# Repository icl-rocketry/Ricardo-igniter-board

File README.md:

# Ricardo-igniter-board
Board that controls pyro channels and monitors pressure for engine igniter.

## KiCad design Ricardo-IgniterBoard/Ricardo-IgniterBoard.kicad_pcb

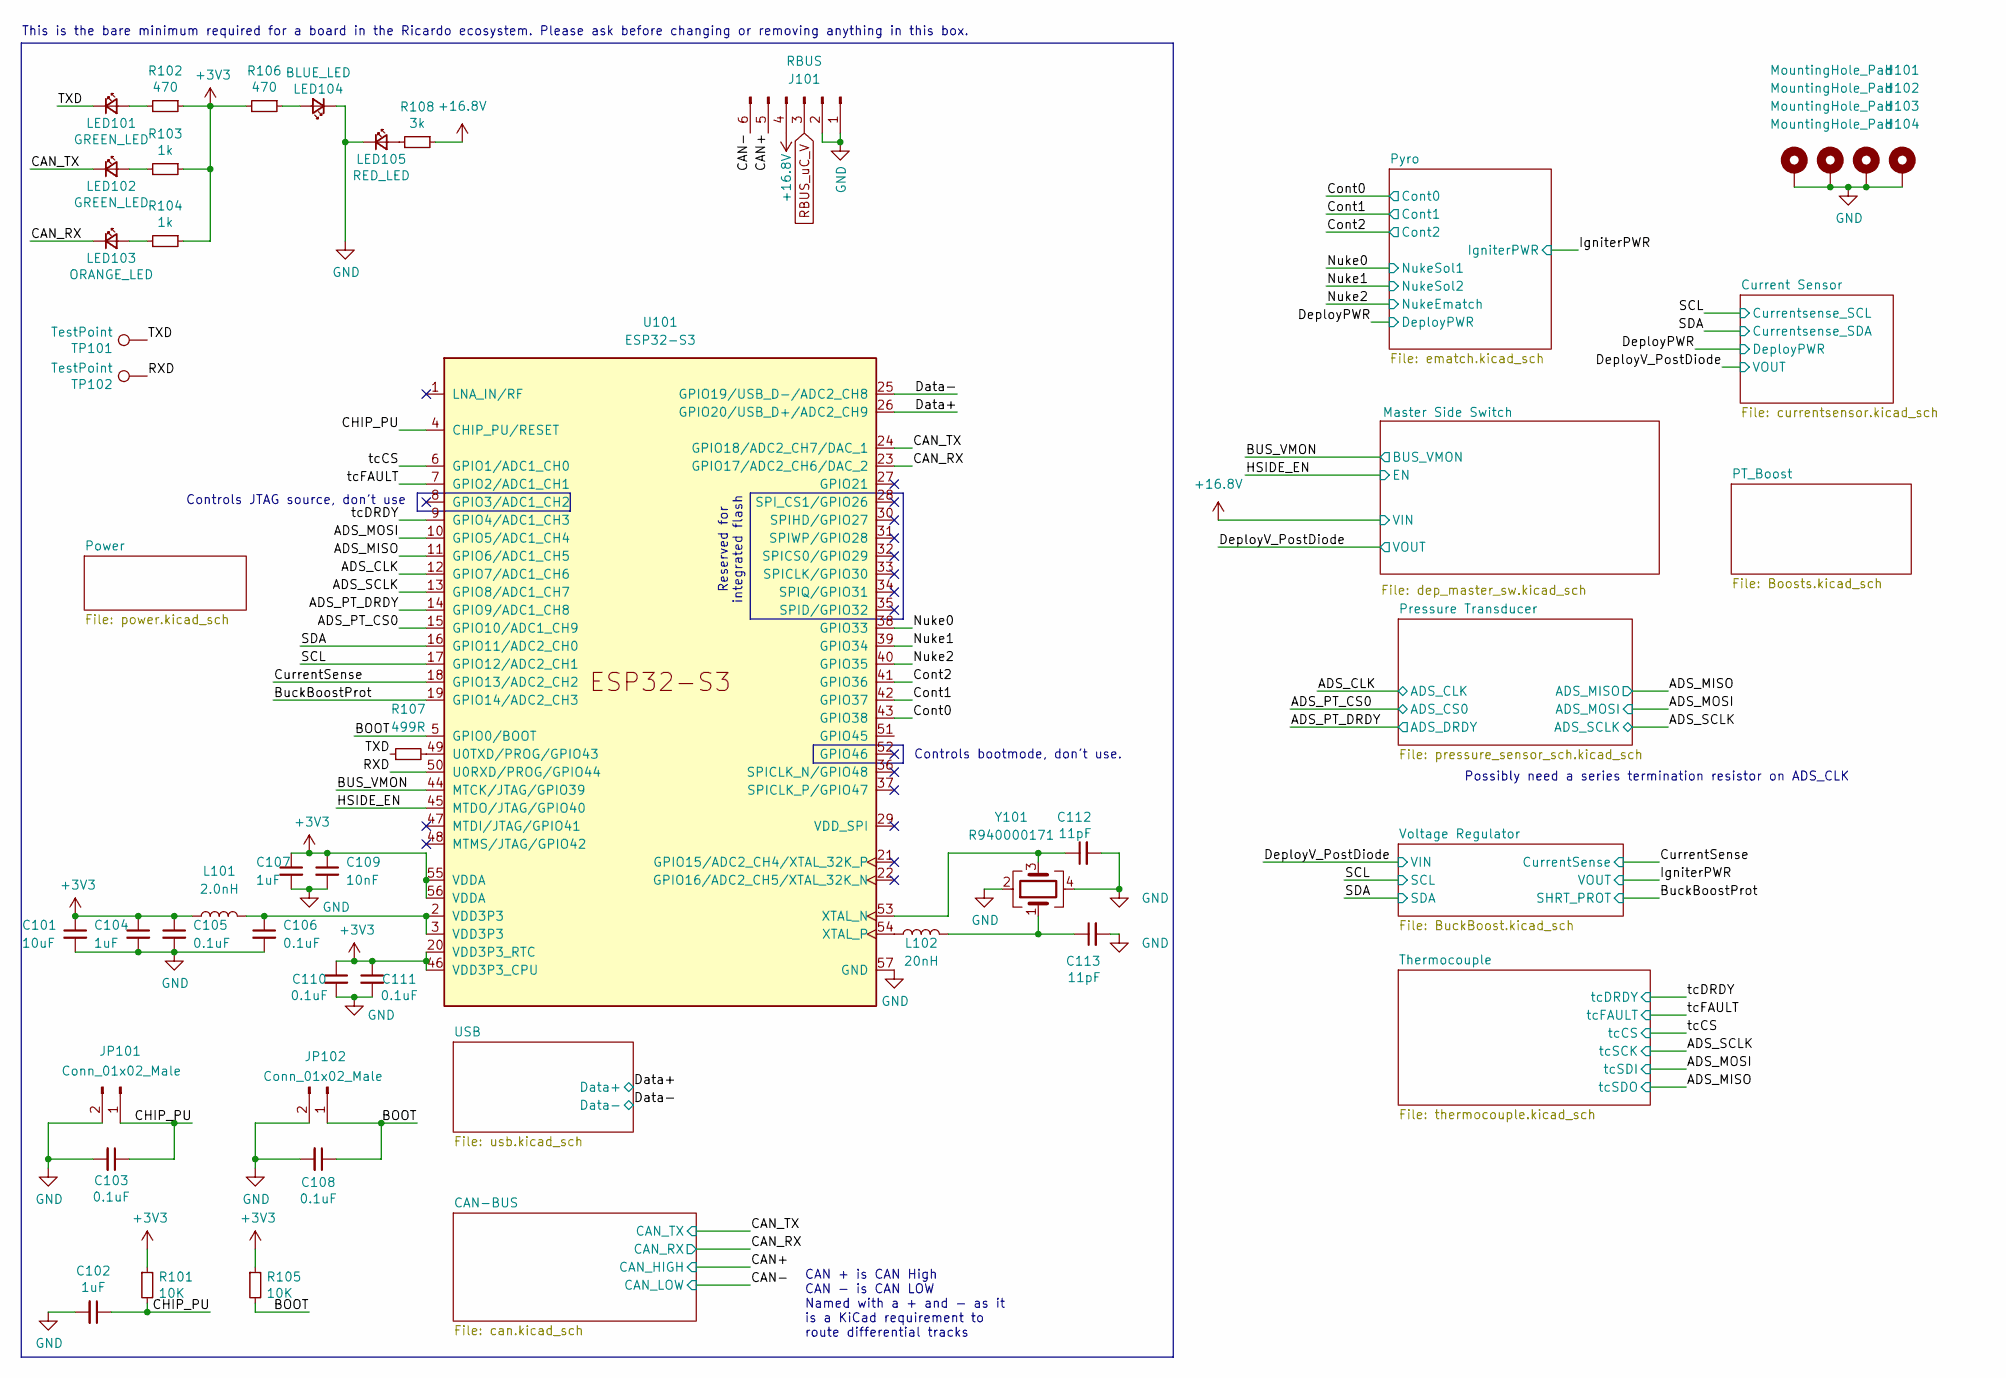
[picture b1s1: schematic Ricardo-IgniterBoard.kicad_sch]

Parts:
C101: 10uF; C_0402_1005Metric
C102, C104, C107: 1uF; C_0402_1005Metric
C103, C105, C106, C108, C110, C111: 0.1uF; C_0402_1005Metric
C109: 10nF; C_0402_1005Metric
C112, C113: 11pF; C_0402_1005Metric
H101, H102, H103, H104: MountingHole_Pad; MountingHole_3.2mm_M3_DIN965_Pad
J101: RBUS; Molex_Mini-Fit_Jr_5569-06A2_2x03_P4.20mm_Horizontal
JP101, JP102: Conn_01x02_Male; PinHeader_1x02_P2.54mm_Vertical
L101: 2.0nH; L_0402_1005Metric
L102: 20nH; L_0402_1005Metric
LED101, LED102: GREEN_LED; LED_0402_1005Metric
LED103: ORANGE_LED; LED_0402_1005Metric
LED104: BLUE_LED; LED_0402_1005Metric
LED105: RED_LED; LED_0402_1005Metric
R101, R105: 10K; R_0402_1005Metric
R102, R106: 470; R_0402_1005Metric
R103, R104: 1k; R_0402_1005Metric
R107: 499R; R_0402_1005Metric
R108: 3k; R_0402_1005Metric
TP101, TP102: TestPoint; TestPoint_Pad_D1.0mm
U101: ESP32-S3; QFN40P700X700X90-57N
Y101: R940000171; Crystal_SMD_2016-4Pin_2.0x1.6mm

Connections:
+3V3: C101.1, C104.1, C105.1, C107.1, C109.1, C110.1, C111.1, L101.1, R101.1, R102.1, R103.1, R104.1, R105.1, R106.2, U101.20 (VDD3P3_RTC), U101.46 (VDD3P3_CPU), U101.55 (VDDA), U101.56 (VDDA); also elsewhere on the board
+16.8V: J101.4, R108.1; also elsewhere on the board
/ADS_CLK: U101.12 (GPIO7/ADC1_CH6); also elsewhere on the board
/ADS_MISO: U101.11 (GPIO6/ADC1_CH5); also elsewhere on the board
/ADS_MOSI: U101.10 (GPIO5/ADC1_CH4); also elsewhere on the board
/ADS_PT_CS0: U101.15 (GPIO10/ADC1_CH9); also elsewhere on the board
/ADS_PT_DRDY: U101.14 (GPIO9/ADC1_CH8); also elsewhere on the board
/ADS_SCLK: U101.13 (GPIO8/ADC1_CH7); also elsewhere on the board
/BOOT: C108.1, JP102.1, R105.2, U101.5 (GPIO0/BOOT)
/BUS_VMON: U101.44 (MTCK/JTAG/GPIO39); also elsewhere on the board
/BuckBoostProt: U101.19 (GPIO14/ADC2_CH3); also elsewhere on the board
/CAN+: J101.5; also elsewhere on the board
/CAN-: J101.6; also elsewhere on the board
/CAN_RX: LED103.1 (K), U101.23 (GPIO17/ADC2_CH6/DAC_2); also elsewhere on the board
/CAN_TX: LED102.1 (K), U101.24 (GPIO18/ADC2_CH7/DAC_1); also elsewhere on the board
/CHIP_PU: C102.1, C103.1, JP101.1, R101.2, U101.4 (CHIP_PU/RESET)
/Cont0: U101.43 (GPIO38); also elsewhere on the board
/Cont1: U101.42 (GPIO37); also elsewhere on the board
/Cont2: U101.41 (GPIO36); also elsewhere on the board
/CurrentSense: U101.18 (GPIO13/ADC2_CH2); also elsewhere on the board
/Data+: U101.26 (GPIO20/USB_D+/ADC2_CH9); also elsewhere on the board
/Data-: U101.25 (GPIO19/USB_D-/ADC2_CH8); also elsewhere on the board
/HSIDE_EN: U101.45 (MTDO/JTAG/GPIO40); also elsewhere on the board
/Nuke0: U101.38 (GPIO33); also elsewhere on the board
/Nuke1: U101.39 (GPIO34); also elsewhere on the board
/Nuke2: U101.40 (GPIO35); also elsewhere on the board
/RXD: TP102.1, U101.50 (U0RXD/PROG/GPIO44)
/SCL: U101.17 (GPIO12/ADC2_CH1); also elsewhere on the board
/SDA: U101.16 (GPIO11/ADC2_CH0); also elsewhere on the board
/TXD: LED101.1 (K), R107.1, TP101.1
/tcCS: U101.6 (GPIO1/ADC1_CH0); also elsewhere on the board
/tcDRDY: U101.9 (GPIO4/ADC1_CH3); also elsewhere on the board
/tcFAULT: U101.7 (GPIO2/ADC1_CH1); also elsewhere on the board
GND: C101.2, C102.2, C103.2, C104.2, C105.2, C106.2, C107.2, C108.2, C109.2, C110.2, C111.2, C112.2, C113.2, H101.1, H102.1, H103.1, H104.1, J101.1, J101.2, JP101.2, JP102.2, LED104.1 (K), LED105.1 (K), U101.57 (GND), Y101.2, Y101.4; also elsewhere on the board
unnamed: C106.1, L101.2, U101.2 (VDD3P3), U101.3 (VDD3P3)
unnamed: C113.1, L102.2, Y101.1
unnamed: LED101.2 (A), R102.2
unnamed: LED102.2 (A), R103.2
unnamed: LED103.2 (A), R104.2
unnamed: LED104.2 (A), R106.1
unnamed: LED105.2 (A), R108.2
unnamed: R107.2, U101.49 (U0TXD/PROG/GPIO43)
unnamed: C112.1, U101.53 (XTAL_N), Y101.3
unnamed: L102.1, U101.54 (XTAL_P)
RBUS_uC_V: J101.3; also elsewhere on the board

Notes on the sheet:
Controls bootmode, don't use.
This is the bare minimum required for a board in the Ricardo ecosystem. Please ask before changing or removing anything in this box.
Possibly need a series termination resistor on ADS_CLK
CAN + is CAN High CAN - is CAN LOW Named with a + and - as it is a KiCad requirement to route differential tracks
Controls JTAG source, don't use
Reserved for integrated flash

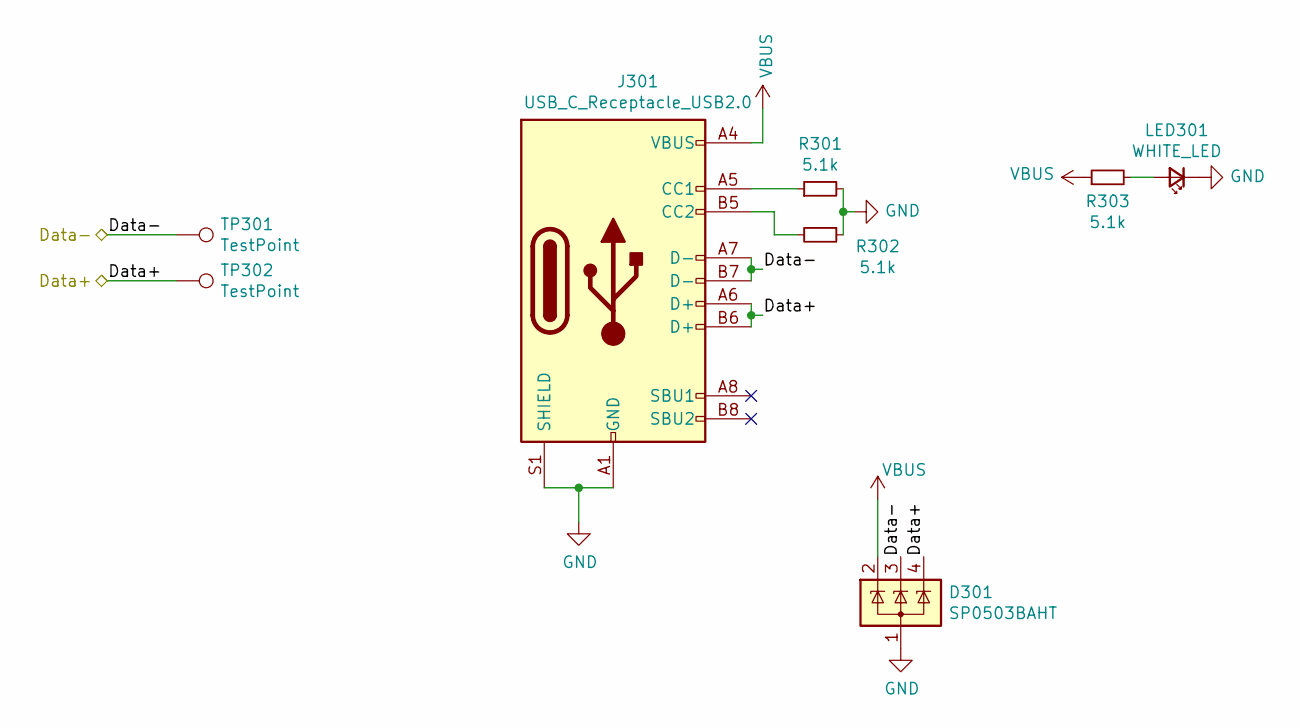
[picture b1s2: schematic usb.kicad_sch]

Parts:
D301: SP0503BAHT; SOT-143
J301: USB_C_Receptacle_USB2.0; USB_C_Receptacle_Palconn_UTC16-G
LED301: WHITE_LED; LED_0402_1005Metric
R301, R302, R303: 5.1k; R_0402_1005Metric
TP301, TP302: TestPoint; TestPoint_Pad_D1.0mm

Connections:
/Data+: D301.4 (K), J301.A6 (D+), J301.B6 (D+), TP302.1; also elsewhere on the board
/Data-: D301.3 (K), J301.A7 (D-), J301.B7 (D-), TP301.1; also elsewhere on the board
GND: D301.1 (A), J301.A1 (GND), J301.A12 (GND), J301.B1 (GND), J301.B12 (GND), J301.S1 (SHIELD), LED301.1 (K), R301.2, R302.1; also elsewhere on the board
unnamed: J301.A5 (CC1), R301.1
unnamed: J301.B5 (CC2), R302.2
unnamed: LED301.2 (A), R303.2
VBUS: D301.2 (K), J301.A4 (VBUS), J301.A9 (VBUS), J301.B4 (VBUS), J301.B9 (VBUS), R303.1; also elsewhere on the board

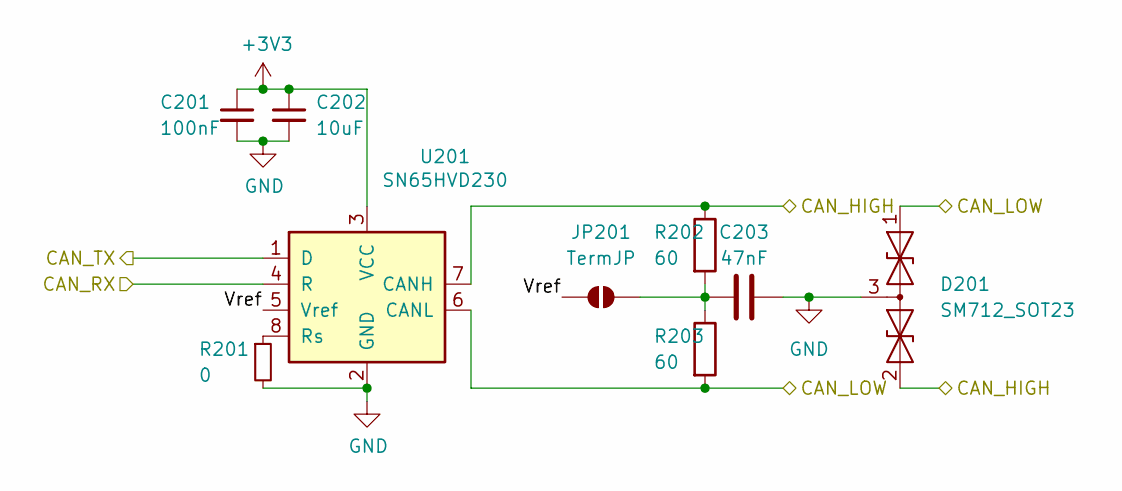
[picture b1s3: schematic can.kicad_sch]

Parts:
C201: 100nF; C_0402_1005Metric
C202: 10uF; C_0402_1005Metric
C203: 47nF; C_0402_1005Metric
D201: SM712_SOT23; SOT-23
JP201: TermJP; SmallerSolderJP
R201: 0; R_0603_1608Metric
R202, R203: 60; R_0603_1608Metric
U201: SN65HVD230; SOIC-8_3.9x4.9mm_P1.27mm

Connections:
+3V3: C201.1, C202.1, U201.3 (VCC); also elsewhere on the board
/CAN+: D201.2 (A2), R202.1, U201.7 (CANH); also elsewhere on the board
/CAN-: D201.1 (A1), R203.2, U201.6 (CANL); also elsewhere on the board
/CAN-BUS/Vref: JP201.1 (A), U201.5 (Vref)
/CAN_RX: U201.4 (R); also elsewhere on the board
/CAN_TX: U201.1 (D); also elsewhere on the board
GND: C201.2, C202.2, C203.2, D201.3 (common), R201.2, U201.2 (GND); also elsewhere on the board
unnamed: C203.1, JP201.2 (B), R202.2, R203.1
unnamed: R201.1, U201.8 (Rs)

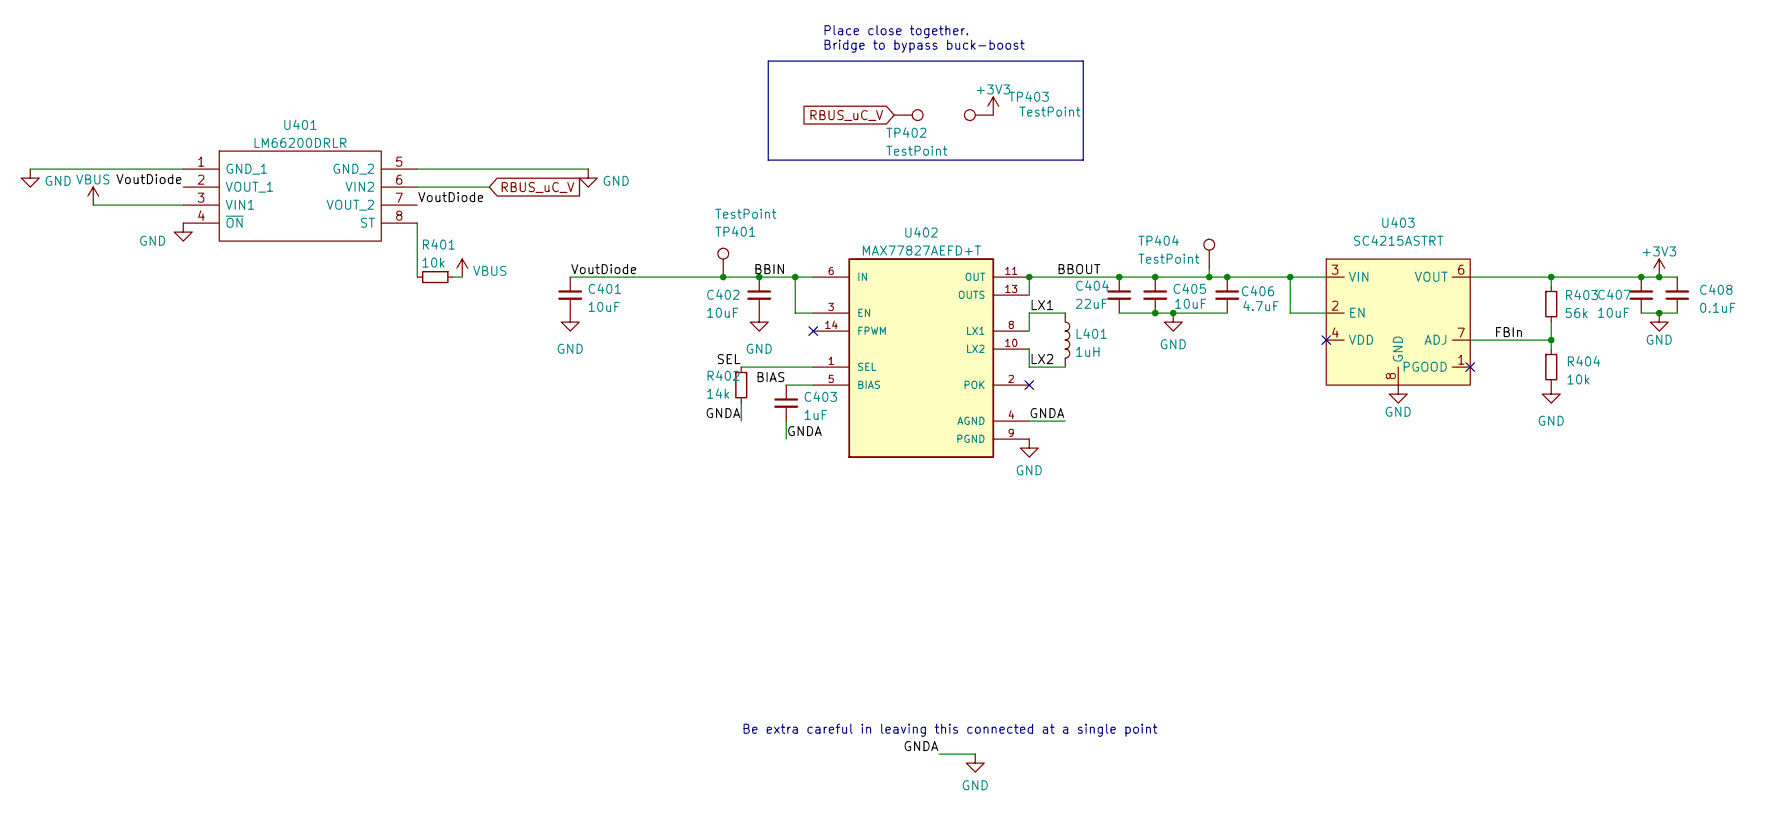
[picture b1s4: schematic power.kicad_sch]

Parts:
C401, C405, C407: 10uF; C_0402_1005Metric
C402: 10uF; C_0603_1608Metric
C403: 1uF; C_0402_1005Metric
C404: 22uF; C_0603_1608Metric
C406: 4.7uF; C_0402_1005Metric
C408: 0.1uF; C_0402_1005Metric
L401: 1uH; L_0805_2012Metric
R401, R404: 10k; R_0402_1005Metric
R402: 14k; R_0402_1005Metric
R403: 56k; R_0402_1005Metric
TP401, TP402, TP403, TP404: TestPoint; TestPoint_Pad_D1.5mm
U401: LM66200DRLR; SOTFL50P160X60-8N; Manufacturer_Part_Number LM66200DRLR; Mouser Part Number 595-LM66200DRLR
U402: MAX77827AEFD+T; CONV_MAX77827AEFD+T; PARTREV B
U403: SC4215ASTRT; SOIC127P599X175-9N

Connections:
+3V3: C407.2, C408.2, R403.1, TP403.1, U403.6 (VOUT); also elsewhere on the board
/Power/BBIN: C401.1, C402.1, TP401.1, U401.2 (VOUT_1), U401.7 (VOUT_2), U402.3 (EN), U402.6 (IN)
/Power/BBOUT: C404.1, C405.1, C406.1, TP404.1, U402.11 (OUT), U402.13 (OUTS), U403.2 (EN), U403.3 (VIN)
/Power/BIAS: C403.1, U402.5 (BIAS)
/Power/FBIn: R403.2, R404.1, U403.7 (ADJ)
/Power/LX1: L401.1, U402.8 (LX1)
/Power/LX2: L401.2, U402.10 (LX2)
/Power/SEL: R402.1, U402.1 (SEL)
GND: C401.2, C402.2, C403.2, C404.2, C405.2, C406.2, C407.1, C408.1, R402.2, R404.2, U401.1 (GND_1), U401.4 (~ON), U401.5 (GND_2), U402.4 (AGND), U402.9 (PGND), U403.8 (GND), U403.9 (GND); also elsewhere on the board
unnamed: R401.2, U401.8 (ST)
RBUS_uC_V: TP402.1, U401.6 (VIN2); also elsewhere on the board
VBUS: R401.1, U401.3 (VIN1); also elsewhere on the board

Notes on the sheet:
Place close together. Bridge to bypass buck-boost
Be extra careful in leaving this connected at a single point

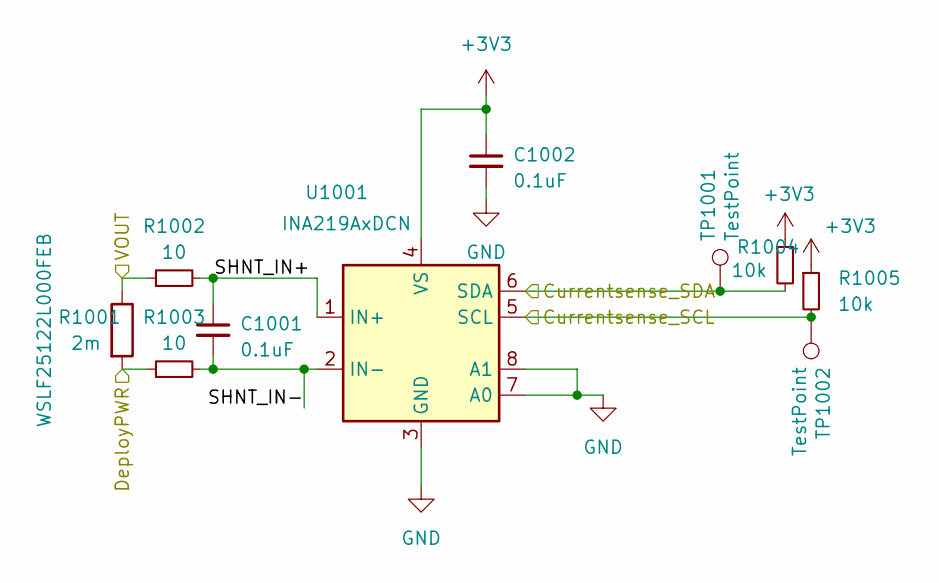
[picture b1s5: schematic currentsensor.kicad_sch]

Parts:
C1001, C1002: 0.1uF; C_0402_1005Metric
R1001: 2m; R_2512_6332Metric_Pad1.40x3.35mm_HandSolder; MPN WSLF25122L000FEB
R1002, R1003: 10; R_0402_1005Metric
R1004, R1005: 10k; R_0402_1005Metric
TP1001, TP1002: TestPoint; TestPoint_Pad_D1.0mm
U1001: INA219AxDCN; SOT-23-8

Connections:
+3V3: C1002.1, R1004.1, R1005.1, U1001.4 (VS); also elsewhere on the board
/Current Sensor/SHNT_IN+: C1001.1, R1002.2, U1001.1 (IN+)
/Current Sensor/SHNT_IN-: C1001.2, R1003.2, U1001.2 (IN-)
/DeployPWR: R1001.2, R1003.1; also elsewhere on the board
/DeployV_PostDiode: R1001.1, R1002.1; also elsewhere on the board
/SCL: R1005.2, TP1002.1, U1001.5 (SCL); also elsewhere on the board
/SDA: R1004.2, TP1001.1, U1001.6 (SDA); also elsewhere on the board
GND: C1002.2, U1001.3 (GND), U1001.7 (A0), U1001.8 (A1); also elsewhere on the board

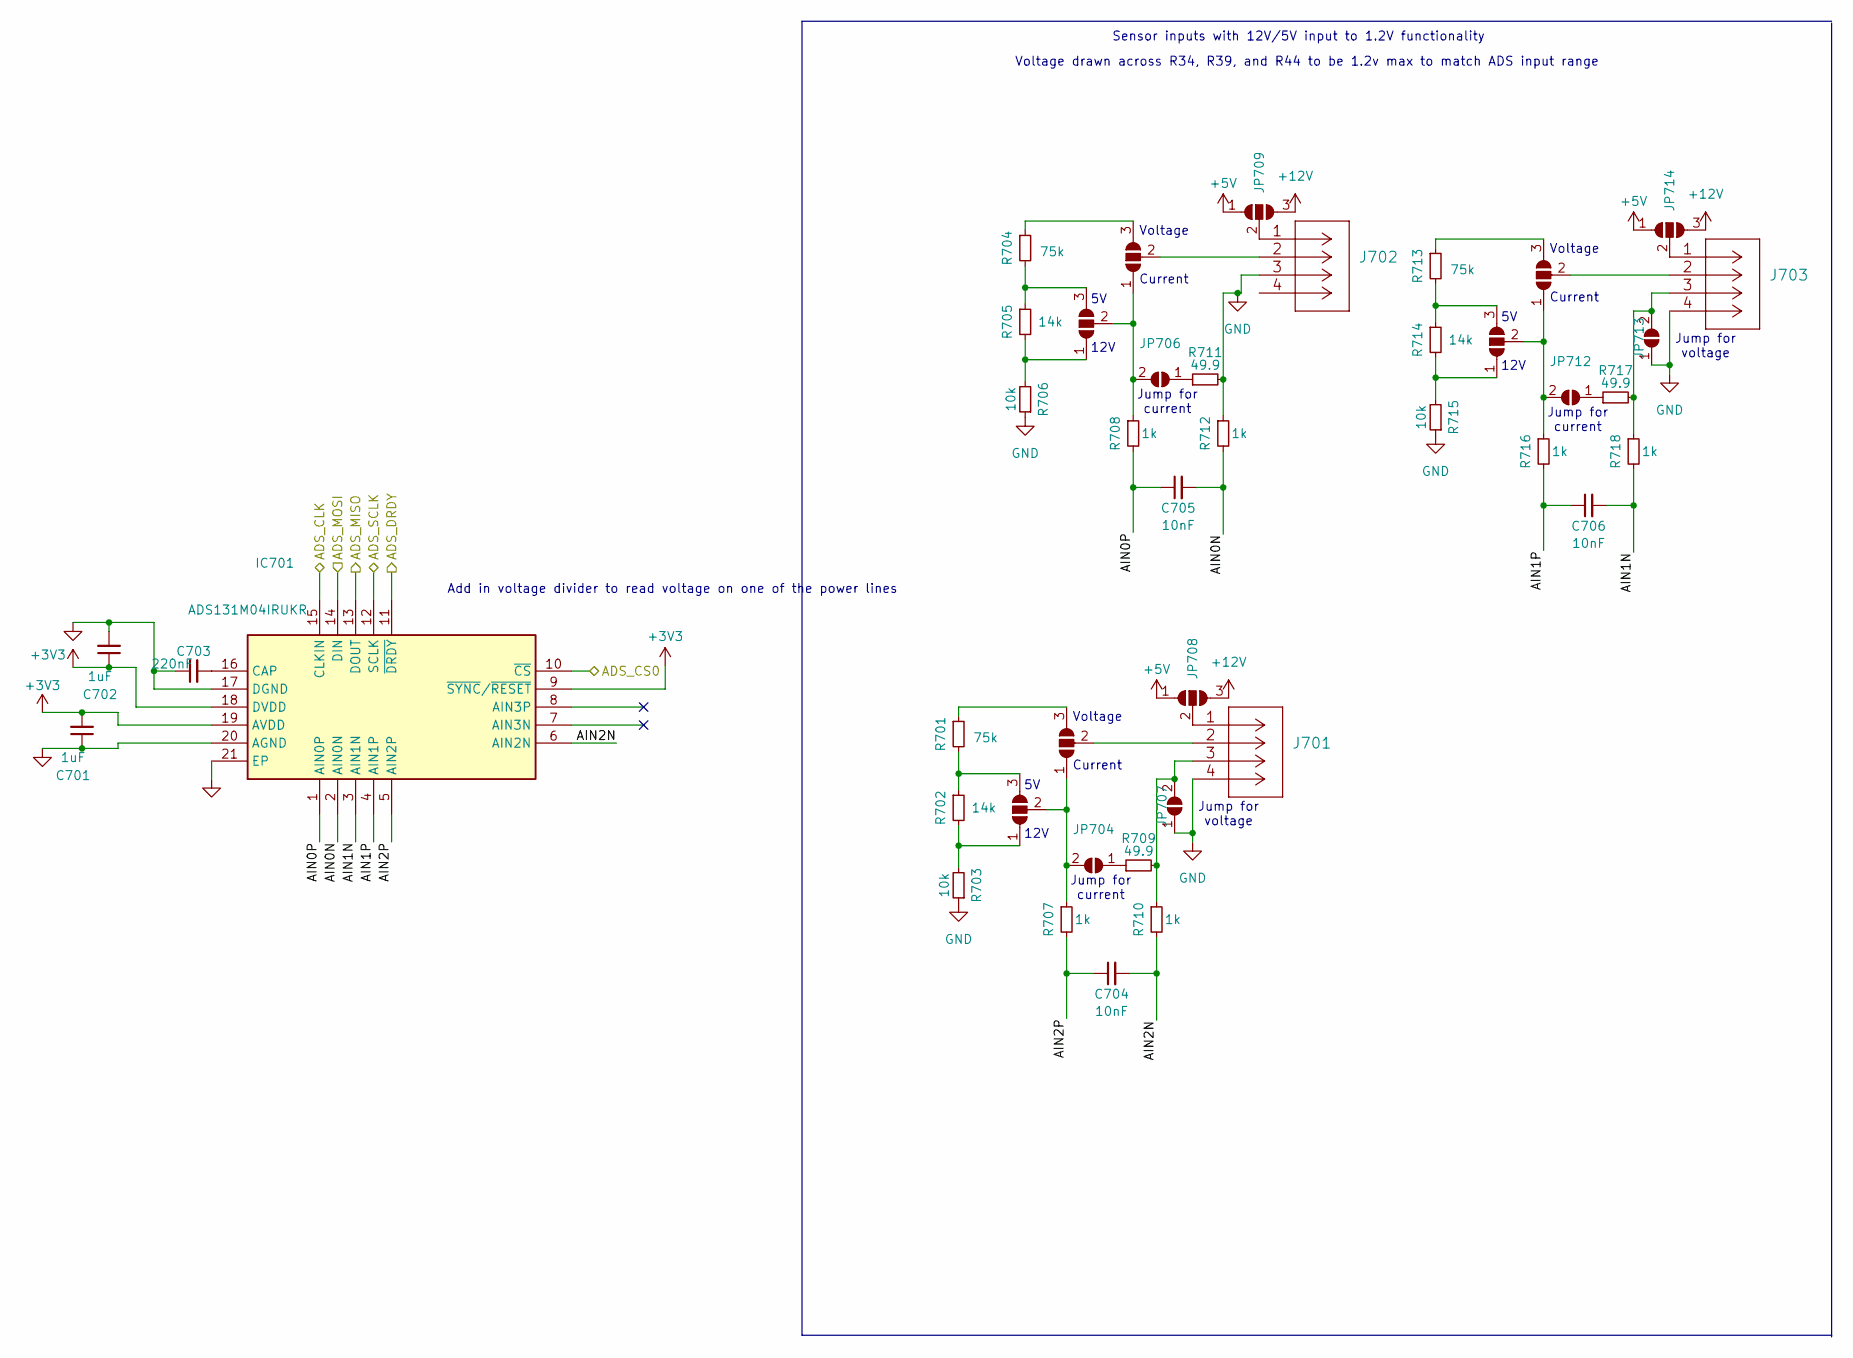
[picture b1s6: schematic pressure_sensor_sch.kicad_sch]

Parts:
C701, C702: 1uF; C_0402_1005Metric
C703: 220nF; C_0402_1005Metric
C704, C705, C706: 10nF; C_0402_1005Metric
IC701: ADS131M04IRUKR; Manufacturer_Part_Number ADS131M04IRUKR; Mouser Part Number 595-ADS131M04IRUKR
J701, J702, J703: 1053131104; Molex_Nano-Fit_105313-xx04_1x04_P2.50mm_Horizontal
JP701, JP702, JP703, JP705, JP708, JP709, JP710, JP711, JP714: SolderJumper_3_Open; SolderJumper-3_P1.3mm_Open_RoundedPad1.0x1.5mm_NumberLabels
JP704, JP706, JP707, JP712, JP713: SolderJumper_2_Open; SmallerSolderJP
R701, R704, R713: 75k; R_0402_1005Metric; MPN RT0402BRD0775KL
R702, R705, R714: 14k; R_0402_1005Metric; MPN 0402WGF1402TCE
R703, R706, R715: 10k; R_0402_1005Metric; MPN ERA2ARB103X
R707, R708, R710, R712, R716, R718: 1k; R_0402_1005Metric
R709, R711, R717: 49.9; R_0402_1005Metric; MPN RT0402BRD0749R9L

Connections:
+3V3: C701.2, C702.1, IC701.9 (~SYNC/~RESET), IC701.18 (DVDD), IC701.19 (AVDD); also elsewhere on the board
+5V: JP708.1 (A), JP709.1 (A), JP714.1 (A)
+12V: JP708.3 (B), JP709.3 (B), JP714.3 (B)
/ADS_CLK: IC701.15 (CLKIN); also elsewhere on the board
/ADS_MISO: IC701.13 (DOUT); also elsewhere on the board
/ADS_MOSI: IC701.14 (DIN); also elsewhere on the board
/ADS_PT_CS0: IC701.10 (~CS); also elsewhere on the board
/ADS_PT_DRDY: IC701.11 (~DRDY); also elsewhere on the board
/ADS_SCLK: IC701.12 (SCLK); also elsewhere on the board
/Pressure Transducer/AIN0N: C705.2, IC701.2 (AIN0N), R712.2
/Pressure Transducer/AIN0P: C705.1, IC701.1 (AIN0P), R708.2
/Pressure Transducer/AIN1N: C706.2, IC701.3 (AIN1N), R718.2
/Pressure Transducer/AIN1P: C706.1, IC701.4 (AIN1P), R716.2
/Pressure Transducer/AIN2N: C704.2, IC701.6 (AIN2N), R710.2
/Pressure Transducer/AIN2P: C704.1, IC701.5 (AIN2P), R707.2
GND: C701.1, C702.2, C703.1, IC701.17 (DGND), IC701.20 (AGND), IC701.21 (EP), J701.4, J702.3, J703.4, JP707.1 (A), JP713.1 (A), R703.1, R706.1, R711.2, R712.1, R715.1; also elsewhere on the board
unnamed: C703.2, IC701.16 (CAP)
unnamed: JP701.1 (A), R702.2, R703.2
unnamed: JP701.3 (B), R701.2, R702.1
unnamed: JP701.2 (C), JP702.1 (A), JP704.2 (B), R707.1
unnamed: JP702.3 (B), R701.1
unnamed: J701.2, JP702.2 (C)
unnamed: JP703.1 (A), R705.2, R706.2
unnamed: JP703.3 (B), R704.2, R705.1
unnamed: JP703.2 (C), JP705.1 (A), JP706.2 (B), R708.1
unnamed: JP704.1 (A), R709.1
unnamed: JP705.3 (B), R704.1
unnamed: J702.2, JP705.2 (C)
unnamed: JP706.1 (A), R711.1
unnamed: J701.3, JP707.2 (B), R709.2, R710.1
unnamed: J701.1, JP708.2 (C)
unnamed: J702.1, JP709.2 (C)
unnamed: JP710.1 (A), R714.2, R715.2
unnamed: JP710.3 (B), R713.2, R714.1
unnamed: JP710.2 (C), JP711.1 (A), JP712.2 (B), R716.1
unnamed: JP711.3 (B), R713.1
unnamed: J703.2, JP711.2 (C)
unnamed: JP712.1 (A), R717.1
unnamed: J703.3, JP713.2 (B), R717.2, R718.1
unnamed: J703.1, JP714.2 (C)

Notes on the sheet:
Voltage
Jump for current
Voltage drawn across R34, R39, and R44 to be 1.2v max to match ADS input range
12V
Current
Add in voltage divider to read voltage on one of the power lines
Jump for voltage
Sensor inputs with 12V/5V input to 1.2V functionality

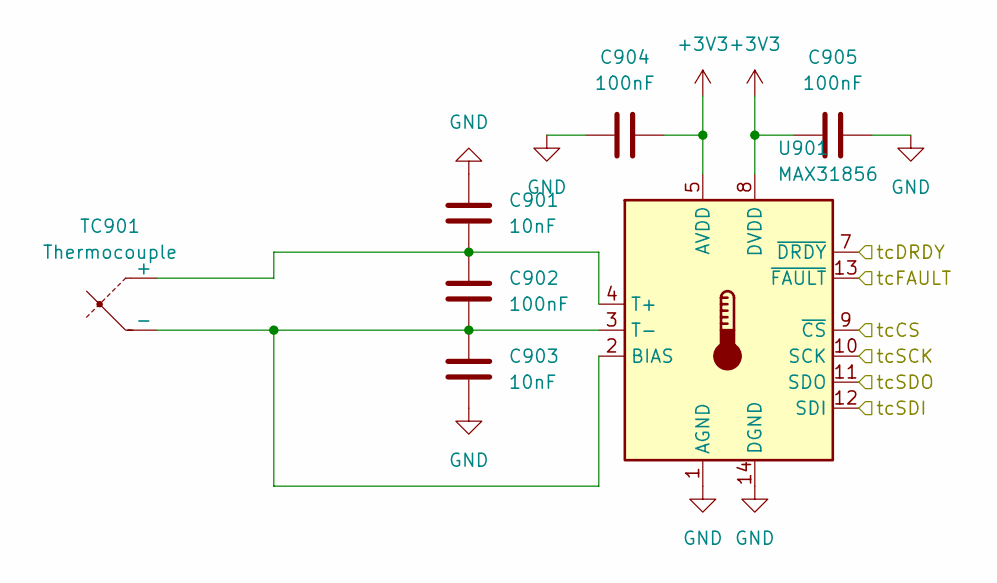
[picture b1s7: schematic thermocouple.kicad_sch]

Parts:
C901, C903: 10nF; C_0402_1005Metric
C902, C904, C905: 100nF; C_0402_1005Metric
TC901: Thermocouple; Molex_Nano-Fit_105313-xx02_1x02_P2.50mm_Horizontal
U901: MAX31856; TSSOP-14_4.4x5mm_P0.65mm

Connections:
+3V3: C904.2, C905.2, U901.5 (AVDD), U901.8 (DVDD); also elsewhere on the board
/ADS_MISO: U901.11 (SDO); also elsewhere on the board
/ADS_MOSI: U901.12 (SDI); also elsewhere on the board
/ADS_SCLK: U901.10 (SCK); also elsewhere on the board
/tcCS: U901.9 (~CS); also elsewhere on the board
/tcDRDY: U901.7 (~DRDY); also elsewhere on the board
/tcFAULT: U901.13 (~FAULT); also elsewhere on the board
GND: C901.1, C903.2, C904.1, C905.1, U901.1 (AGND), U901.14 (DGND); also elsewhere on the board
unnamed: C901.2, C902.1, TC901.1 (+), U901.4 (T+)
unnamed: C902.2, C903.1, TC901.2 (-), U901.2 (BIAS), U901.3 (T-)

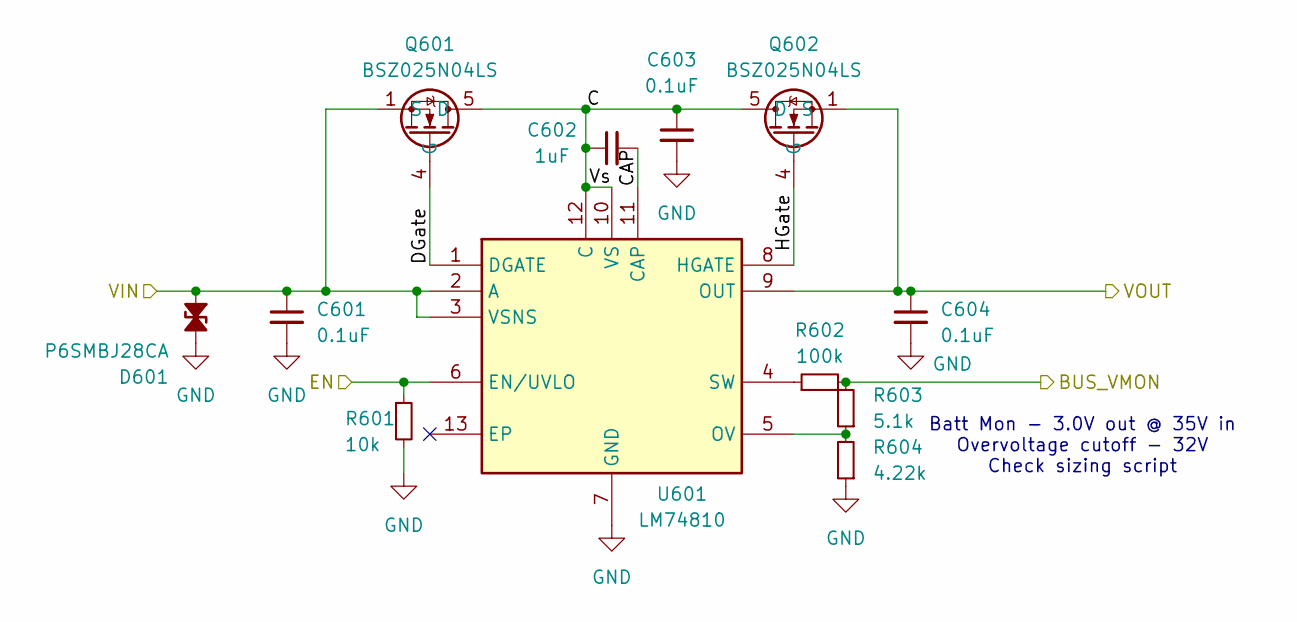
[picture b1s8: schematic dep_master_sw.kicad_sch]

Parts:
C601, C604: 0.1uF; C_0402_1005Metric
C602: 1uF; C_0402_1005Metric; Voltage Rating DC 50V; MPN GRT188R61H225KE13D
C603: 0.1uF; C_0603_1608Metric
D601: P6SMBJ28CA; D_SMA
Q601, Q602: BSZ025N04LS; Manufacturer_Part_Number BSZ025N04LS; Mouser Part Number 726-BSZ025N04LS
R601: 10k; R_0402_1005Metric
R602: 100k; R_0402_1005Metric
R603: 5.1k; R_0402_1005Metric
R604: 4.22k; R_0402_1005Metric
U601: LM74810; SON50P300X300X80-13N-D; Manufacturer_Part_Number LM74810QDRRRQ1; Mouser Part Number 595-LM74810QDRRRQ1

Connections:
+16.8V: C601.1, D601.1 (A1), Q601.1 (S), Q601.2 (S), Q601.3 (S), Q601.A1 (S), U601.2 (A), U601.3 (VSNS); also elsewhere on the board
/BUS_VMON: R602.2, R603.2; also elsewhere on the board
/DeployV_PostDiode: C604.1, Q602.1 (S), Q602.2 (S), Q602.3 (S), Q602.A1 (S), U601.9 (OUT); also elsewhere on the board
/HSIDE_EN: R601.1, U601.6 (EN/UVLO); also elsewhere on the board
/Master Side Switch/C: C602.1, C603.1, Q601.5 (D), Q601.6 (D), Q601.7 (D), Q601.8 (D), Q601.A5 (D), Q602.5 (D), Q602.6 (D), Q602.7 (D), Q602.8 (D), Q602.A5 (D), U601.10 (VS), U601.12 (C)
/Master Side Switch/CAP: C602.2, U601.11 (CAP)
/Master Side Switch/DGate: Q601.4 (G), U601.1 (DGATE)
/Master Side Switch/HGate: Q602.4 (G), U601.8 (HGATE)
GND: C601.2, C603.2, C604.2, D601.2 (A2), R601.2, R604.1, U601.7 (GND); also elsewhere on the board
unnamed: R603.1, R604.2, U601.5 (OV)
unnamed: R602.1, U601.4 (SW)

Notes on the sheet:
Batt Mon - 3.0V out @ 35V in Overvoltage cutoff - 32V Check sizing script

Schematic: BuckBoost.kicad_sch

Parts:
Cboot801, Cboot802: 100nF; C_0402_1005Metric
Ccomp801: 15pF; C_0402_1005Metric
Ccomp802: 2.2nF; C_0402_1005Metric
Cdith801: 8.2nF; C_0402_1005Metric
Cin801: 82uF; CP_EIA-6032-28_Kemet-C
Cinx801: 10uF; C_0402_1005Metric
Cout801, Cout802: 56uF; CP_EIA-6032-28_Kemet-C
Coutx801, Coutx802, Coutx803: 15uF; C_0402_1005Metric
Cvcc801: 4.7uF; C_0402_1005Metric
L801: 5.6uH; PA4344562NLT
LED801: RED_LED; LED_0402_1005Metric
Q801, Q802: BSZ025N04LS; Manufacturer_Part_Number BSZ025N04LS; Mouser Part Number 726-BSZ025N04LS
R801: 715k; R_0402_1005Metric
R802: 100k; R_0402_1005Metric
R803: 49.9k; R_0402_1005Metric
R804, R805: 1; R_0402_1005Metric
R806: 3k; R_0402_1005Metric
Rcomp801: 95.3k; R_0402_1005Metric
Rlim801: 31.6k; R_0402_1005Metric
Rsns801: 8.333m; R_0402_1005Metric
U801: TPS55288QRPMRQ1; CONV_TPS552882QRPMRQ1; Mouser Part Number 595-TPS55288QRPMRQ1

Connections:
/BuckBoostProt: U801.14 (FB/~INT); also elsewhere on the board
/CurrentSense: U801.16 (CDC); also elsewhere on the board
/DeployV_PostDiode: Cin801.1, Cinx801.1, Q801.5 (D), Q801.6 (D), Q801.7 (D), Q801.8 (D), Q801.A5 (D), R801.1, U801.3 (VIN); also elsewhere on the board
/IgniterPWR: R806.1, Rsns801.2, U801.13 (ISN_1), U801.29 (ISN_2); also elsewhere on the board
/SCL: U801.5 (SCL); also elsewhere on the board
/SDA: U801.6 (SDA); also elsewhere on the board
/Voltage Regulator/DITH_2: Cdith801.2, U801.7 (DITH/SYNC_1), U801.28 (DITH/SYNC_2)
/Voltage Regulator/SW2_2: Cboot801.2, L801.1, U801.21 (SW2_1), U801.25 (SW2_2)
/Voltage Regulator/VCC_2: Cvcc801.1, U801.19 (VCC_1), U801.30 (VCC_2)
/Voltage Regulator/VOUT_2: Cout801.1, Cout802.1, Coutx801.1, Coutx802.1, Coutx803.1, Rsns801.1, U801.11 (VOUT_1), U801.12 (ISP), U801.26 (VOUT_2)
GND: Ccomp801.2, Cdith801.1, Cin801.2, Cinx801.2, Cout801.2, Cout802.2, Coutx801.2, Coutx802.2, Coutx803.2, Cvcc801.2, LED801.1 (K), Q802.1 (S), Q802.2 (S), Q802.3 (S), Q802.A1 (S), R802.2, R803.1, Rcomp801.2, Rlim801.2, U801.9 (PGND_1), U801.10 (AGND), U801.15 (MODE), U801.24 (PGND_2); also elsewhere on the board
unnamed: Ccomp802.2, Rcomp801.1
unnamed: LED801.2 (A), R806.2
unnamed: Q801.4 (G), R804.1
unnamed: Q802.4 (G), R805.1
unnamed: Cboot802.1, U801.22 (BOOT1)
unnamed: Cboot801.1, U801.20 (BOOT2)
unnamed: Ccomp801.1, Ccomp802.1, U801.18 (COMP)
unnamed: R804.2, U801.2 (DR1H)
unnamed: R805.2, U801.1 (DR1L_1)
unnamed: R801.2, R802.1, U801.4 (EN/UVLO)
unnamed: R803.2, U801.8 (FSW)
unnamed: Rlim801.1, U801.17 (ILIM)
unnamed: Cboot802.2, L801.2, Q801.1 (S), Q801.2 (S), Q801.3 (S), Q801.A1 (S), Q802.5 (D), Q802.6 (D), Q802.7 (D), Q802.8 (D), Q802.A5 (D), U801.23 (SW1)

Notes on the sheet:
Didn't change either of these from their source (Crosshair and flint and steel)
OUTPUT CURRENT SENSING: V_CDC = 20 × (V_ISP - V_ISN)

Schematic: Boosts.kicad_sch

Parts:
C1101: 10uF; C_0603_1608Metric
C1102: 180pF; C_0402_1005Metric
C1103: 3.9nF; C_0402_1005Metric
C1104: 1uF; C_0402_1005Metric
C1105, C1106: 22uF; C_0805_2012Metric
C1107, C1109, C1112: 100nF; C_0402_1005Metric
C1108: 2.2uF; C_0402_1005Metric
C1110: 47uF; C_1206_3216Metric
C1111: 10uF; C_0402_1005Metric
IC1101: TPS61089RNRR; IC_TPS61089RNRR; Manufacturer_Part_Number TPS61089RNRR; Mouser Part Number 595-TPS61089RNRR
IC1102: AP2205-W5-7; SOT95P282X145-5N; Mouser Part Number 621-AP2205-W5-7
L1101: SRR6038-5R0Y; SRR6038; Manufacturer_Part_Number SRR6038-5R0Y; Mouser Part Number 652-SRR6038-5R0Y
R1101: 7.87k; R_0402_1005Metric
R1102: 360k; R_0402_1005Metric
R1103: 100k; R_0402_1005Metric
R1104: 560k; R_0402_1005Metric
R1105: 50k; R_0402_1005Metric
R1106: 152k; R_0603_1608Metric
R1107: 309k; R_0402_1005Metric

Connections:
+3.3V: C1109.1, C1110.1, IC1101.9 (VIN), L1101.1
/PT_Boost/5V: C1108.1, IC1102.5 (VOUT), R1106.2
/PT_Boost/FB_5V: IC1101.3 (FB), R1102.1, R1103.2
/PT_Boost/LDO5.5V_IN: C1104.1, C1105.1, C1106.1, C1111.1, C1112.1, IC1101.6 (VOUT), IC1102.1 (VIN), IC1102.3 (EN), R1102.2
/PT_Boost/SW_5V: IC1101.1 (FSW), R1107.1
GND: C1101.2, C1102.2, C1103.2, C1104.2, C1105.2, C1106.2, C1108.2, C1109.2, C1110.2, C1111.2, C1112.2, IC1101.5 (GND), IC1102.2 (GND), R1103.1, R1104.1, R1105.1; also elsewhere on the board
unnamed: C1103.1, R1101.2
unnamed: C1107.1, IC1101.10 (BOOT)
unnamed: C1102.1, IC1101.4 (COMP), R1101.1
unnamed: C1101.1, IC1101.2 (VCC), IC1101.7 (EN)
unnamed: IC1101.8 (ILIM), R1104.2
unnamed: C1107.2, IC1101.11 (SW), L1101.2, R1107.2
unnamed: IC1102.4 (ADJ/NC), R1105.2, R1106.1

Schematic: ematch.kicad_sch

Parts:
D501, D502, D509: V8PAM10S-M3/I; V8PAM10SM3I
D503, D504, D510: DST1550S; TO-277B
D505, D506, D511: RED_LED; LED_0603_1608Metric
D507, D508, D512: S-102T; SODFL3516X70N; Manufacturer_Part_Number S-102T; Mouser Part Number 954-S-102T
Firing501, Firing502, Firing503: EMERALD_LED; LED_0402_1005Metric
J501, J502, J503: Conn_01x02_Male; TerminalBlock_Phoenix_PT-1,5-2-3.5-H_1x02_P3.50mm_Horizontal
Q501, Q502, Q503: BSZ025N04LS; Manufacturer_Part_Number BSZ025N04LS; Mouser Part Number 726-BSZ025N04LS
R501, R502, R507: 120; R_0402_1005Metric
R503, R504, R508: 10K; R_0402_1005Metric
R505, R506, R509: 120; R_0603_1608Metric
U3, U4: LTV-247; SOP-16_4.4x10.4mm_P1.27mm

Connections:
+3V3: U4.12, U4.14, U4.15; also elsewhere on the board
/Cont0: R505.1, U4.11; also elsewhere on the board
/Cont1: R506.1, U4.13; also elsewhere on the board
/Cont2: R509.1, U4.16; also elsewhere on the board
/DeployPWR: D501.1 (K), D502.1 (K), J501.1, J502.1; also elsewhere on the board
/IgniterPWR: D509.1 (K), J503.1; also elsewhere on the board
/Nuke0: Firing501.2 (A), Q501.4 (G), R503.1; also elsewhere on the board
/Nuke1: Firing502.2 (A), Q502.4 (G), R504.1; also elsewhere on the board
/Nuke2: Firing503.2 (A), Q503.4 (G), R508.1; also elsewhere on the board
GND: D505.1 (K), D506.1 (K), D507.1 (K), D508.1 (K), D511.1 (K), D512.1 (K), Q501.1 (S), Q501.2 (S), Q501.3 (S), Q501.A1 (S), Q502.1 (S), Q502.2 (S), Q502.3 (S), Q502.A1 (S), Q503.1 (S), Q503.2 (S), Q503.3 (S), Q503.A1 (S), R501.2, R502.2, R503.2, R504.2, R507.2, R508.2; also elsewhere on the board
unnamed: D501.2 (A), D503.1 (A), D503.2 (A), J501.2, U4.5
unnamed: D502.2 (A), D504.1 (A), D504.2 (A), J502.2, U4.3
unnamed: D503.3 (K), Q501.5 (D), Q501.6 (D), Q501.7 (D), Q501.8 (D), Q501.A5 (D)
unnamed: D504.3 (K), Q502.5 (D), Q502.6 (D), Q502.7 (D), Q502.8 (D), Q502.A5 (D)
unnamed: D505.2 (A), R505.2
unnamed: D506.2 (A), R506.2
unnamed: D507.2 (A), U4.6
unnamed: D508.2 (A), U4.4
unnamed: D509.2 (A), D510.1 (A), D510.2 (A), J503.2, U4.2
unnamed: D510.3 (K), Q503.5 (D), Q503.6 (D), Q503.7 (D), Q503.8 (D), Q503.A5 (D)
unnamed: D511.2 (A), R509.2
unnamed: D512.2 (A), U4.1
unnamed: Firing501.1 (K), R501.1
unnamed: Firing502.1 (K), R502.1
unnamed: Firing503.1 (K), R507.1

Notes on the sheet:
Ematch
Soleinoid
LTV 247 is a single chip represented by multiple smaller chips
